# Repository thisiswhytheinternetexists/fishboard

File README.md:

# FishBoard
## An Oak-Based controller for 12 Volts aquarium device control

Basic useful feature list:

- [ ] Switches LED strips on and off on a schedule or triggered by a REST call (REST call works, schedule is untested)
- [X] Allows up to 3 devices to be controlled (channel 1 and 2 work, todo: channel 3 troubleshooting)
- [ ] Manual override using buttons (doesn't currently work, todo: hardware troubleshooting)
- [X] Connects to your existing 2.4GHz WiFi Network for remote control and management (handled by the Oak Config, todo: write guide)
- [ ] Supports an SSD1306 OLED display for status and standalone operation
- [X] Integration with Domoticz (todo: write guide. Is a shell script that does a [particle API call](https://docs.particle.io/reference/firmware/photon/#particle-function-))

BOM:

| Manufacturer       | P/N            | Amount |
| ------------------ | -------------- | ------ |
| Multicomp          | MJ-179PH       | 1      |
| Fairchild          | FQP30N06L      | 3      |
| Multicomp          | 1N5819         | 3      |
| WURTH Elektronik   | 61300911121    | 2      |
| DigiStump          | Oak            | 1      |
| TE Connectivity    | CFR16J10K      | 1      | 
| Molex              | 22-23-2021     | 7      |
| Molex              | 22-01-2027     | 7      |
| Molex              | 08-50-0032     | 14     |
| Multicomp          | R13-24AL-05-BB | 4      |
| DELTRON ENCLOSURES | 479-0140-0     | 1      |
| Pro Power          | PPW00030       | 2      |
 
Total BOM cost (excluding Oak and PCB) is roughly about EUR14.

Datasheet for MOSFET: http://www.mouser.com/ds/2/149/FQP30N06L-244344.pdf
Datasheet for enclosure: http://www.farnell.com/datasheets/1792140.pdf

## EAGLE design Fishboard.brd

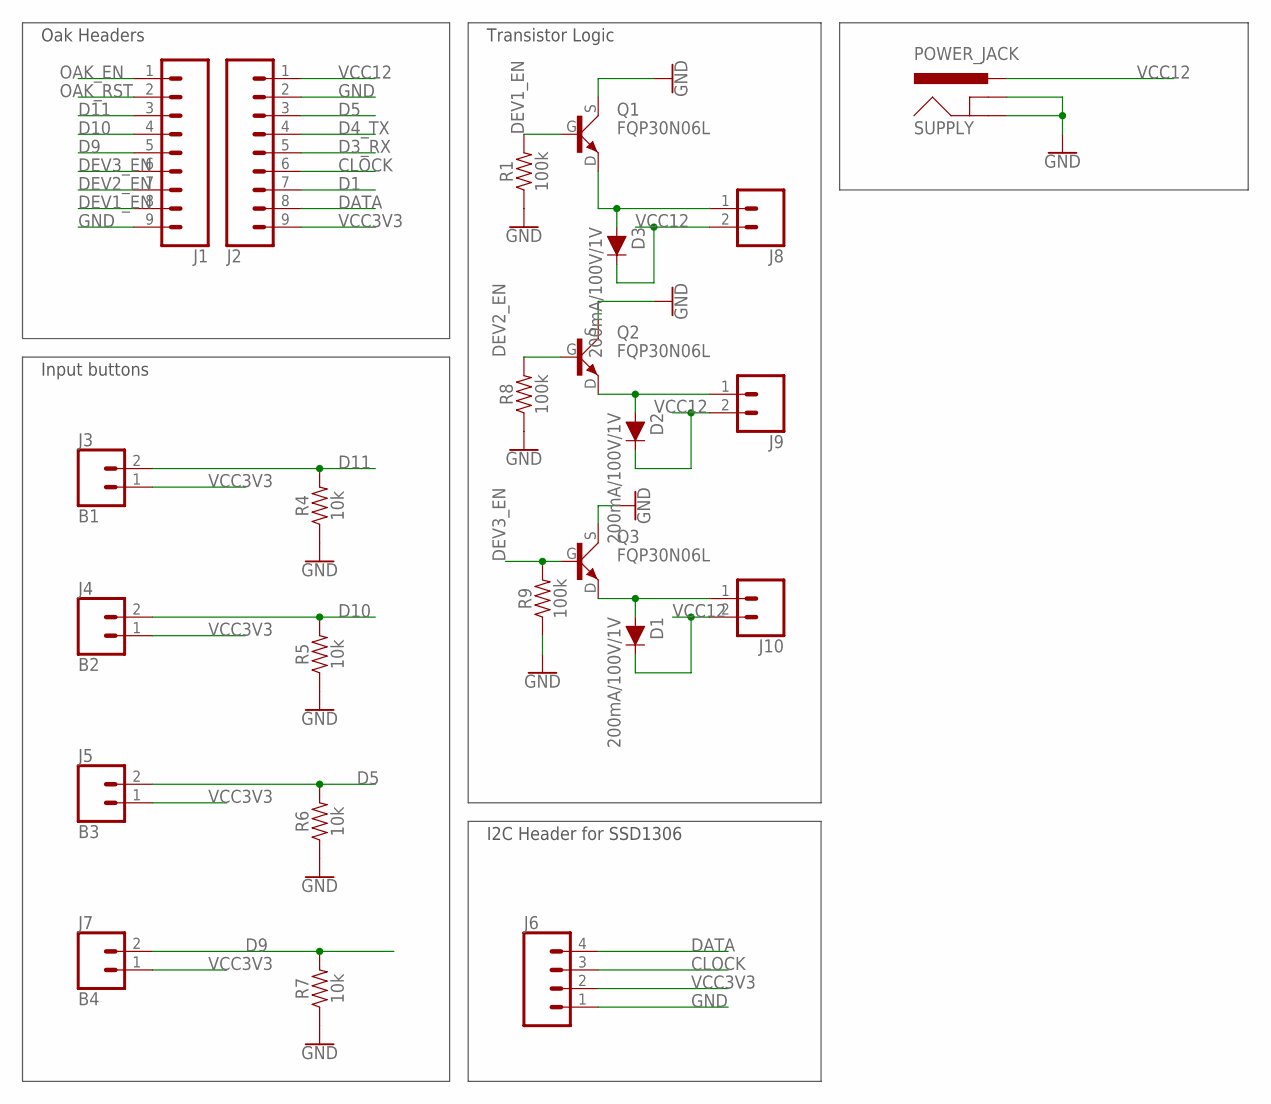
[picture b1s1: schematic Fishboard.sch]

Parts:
D1, D2, D3: 200mA/100V/1V; DIODE-1N4148-KIT
J1, J2: CONN_09LOCK; 1X09_LOCK
J3: B1; 1X02_LOCK
J4: B2; 1X02_LOCK
J5: B3; 1X02_LOCK
J6: CONN_04LOCK; 1X04_LOCK
J7: B4; 1X02_LOCK
J8, J9, J10: CONN_02PTH3; 1X02_LONGPADS
Q1, Q2, Q3: FQP30N06L; TO220
R1, R8, R9: 100k; AXIAL-0.3
R4, R5, R6, R7: 10k; AXIAL-0.3
SUPPLY: POWER_JACK; POWER_JACK_PTH

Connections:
CLOCK: J2.6, J6.3
D1: J2.7
D3_RX: J2.5
D4_TX: J2.4
D5: J2.3, J5.2, R6.P$2 (2)
D9: J1.5, J7.2, R7.P$2 (2)
D10: J1.4, J4.2, R5.P$2 (2)
D11: J1.3, J3.2, R4.P$2 (2)
DATA: J2.8, J6.4
DEV1_EN: J1.8, Q1.G (1), R1.P$2 (2)
DEV2_EN: J1.7, Q2.G (1), R8.P$2 (2)
DEV3_EN: J1.6, Q3.G (1), R9.P$2 (2)
GND: J1.9, J2.2, J6.1, Q1.S (3), Q2.S (3), Q3.S (3), R1.P$1 (1), R4.P$1 (1), R5.P$1 (1), R6.P$1 (1), R7.P$1 (1), R8.P$1 (1), R9.P$1 (1), SUPPLY.GND, SUPPLY.GNDBREAK
unnamed: D2.A, J9.1, Q2.D (2)
unnamed: D3.A, J8.1, Q1.D (2)
unnamed: D1.A, J10.1, Q3.D (2)
OAK_EN: J1.1
OAK_RST: J1.2
VCC3V3: J2.9, J3.1, J4.1, J5.1, J6.2, J7.1
VCC12: D1.C, D2.C, D3.C, J2.1, J8.2, J9.2, J10.2, SUPPLY.PWR

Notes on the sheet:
Oak Headers
Input buttons
I2C Header for SSD1306
Transistor Logic

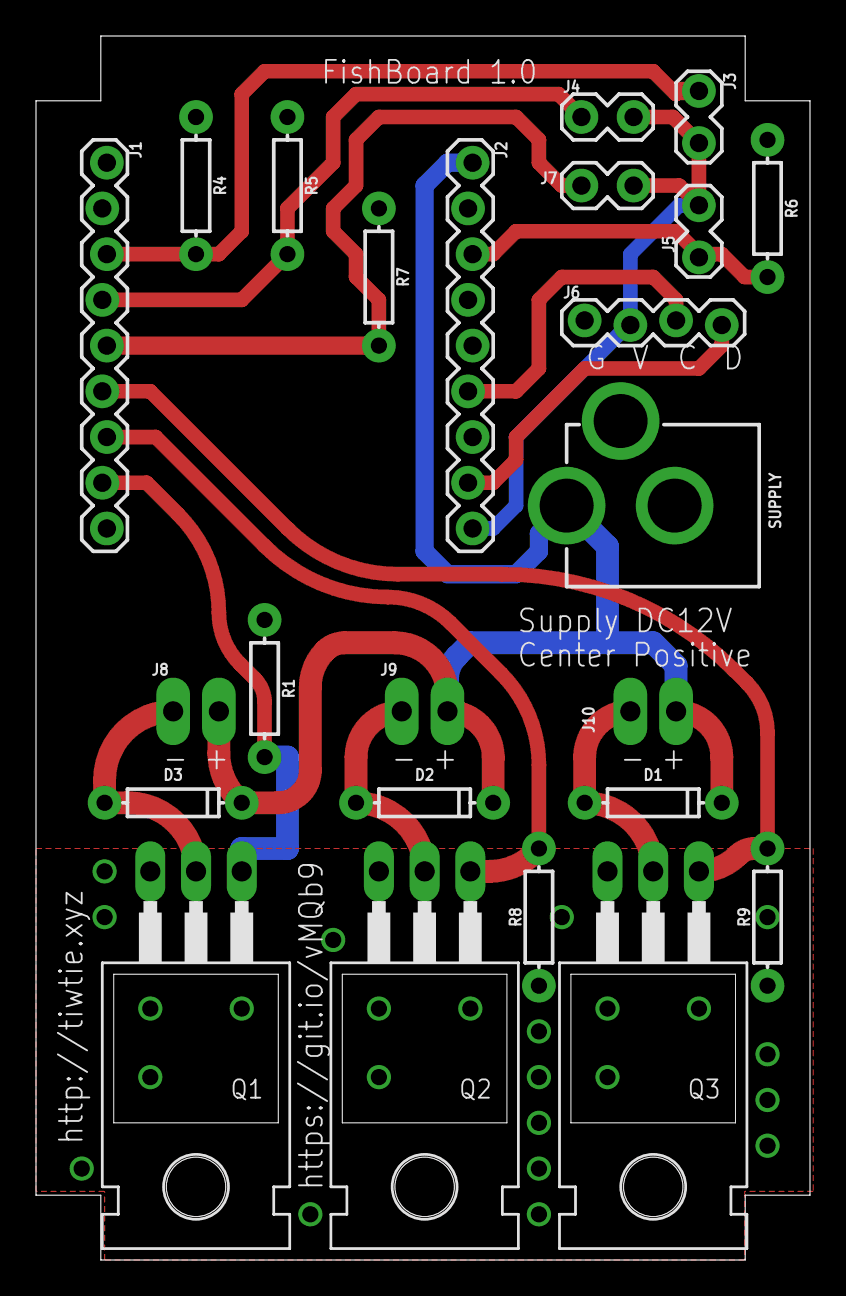
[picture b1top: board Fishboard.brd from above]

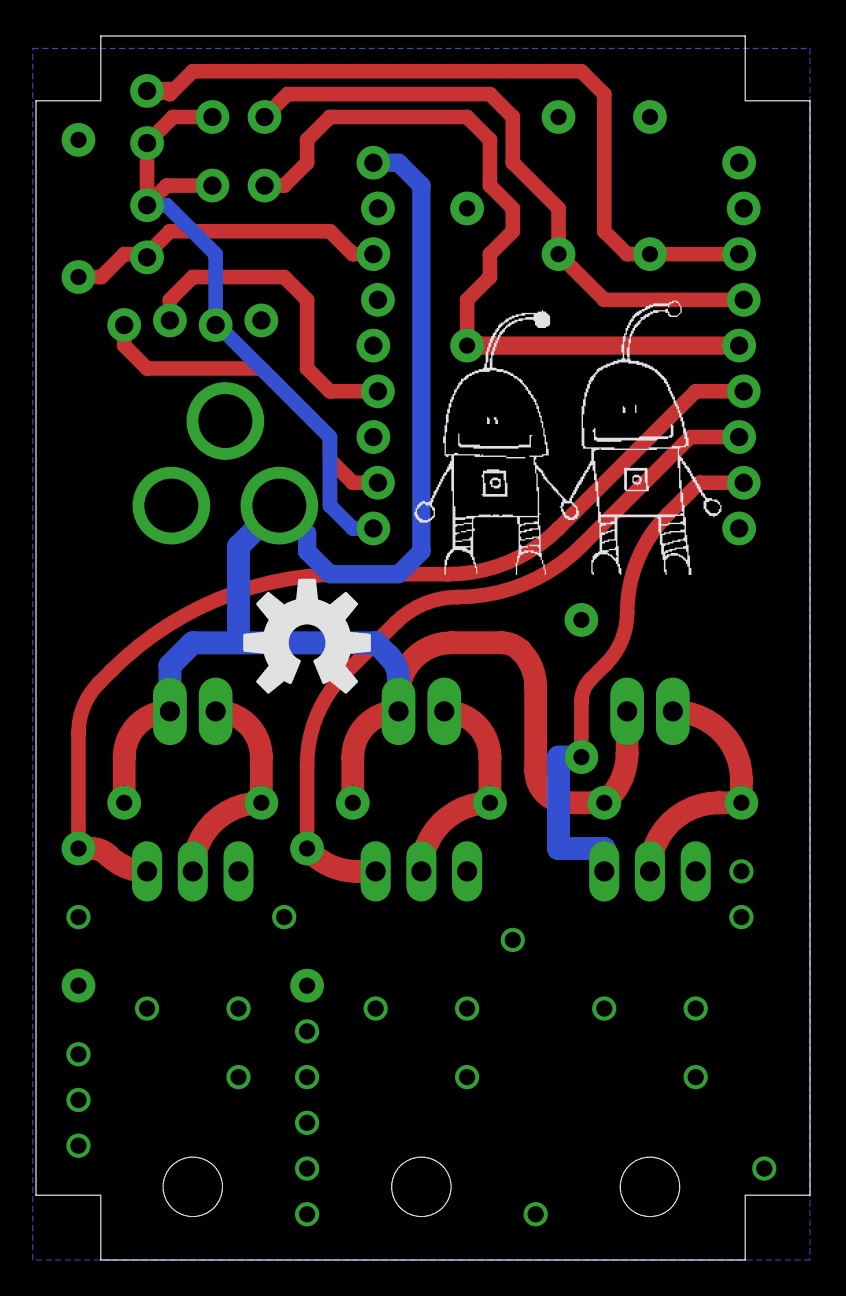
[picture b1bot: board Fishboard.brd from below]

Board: 2 copper layers, 43.0 x 68.0 mm, 26 parts (2 on the bottom side), 15 nets.

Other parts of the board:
U$1: TIWTIE_LOGO
U$2: OSHW-LOGO-L

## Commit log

2017-01-22 Initial commit. I'll have this reviewed by someone before sending it off to the fab :)
2017-01-22 Reorganized schematics
2017-01-22 Switched the TIP120 with a logic level MOSFET (FQP30N06L). The current limiting resistors have been replaced with pulldowns.
2017-01-22 Added library with a custom part
2017-01-22 Replaced TIP120 part with custom part so that we can correctly route it.
2017-01-22 Added reference to MOSFET datasheet in README.md
2017-01-29 Moved Open Source Hardware logo to bottom of board. Added flyback diodes.
2017-01-29 Changed the board size and rerouted everything to make the board fit the case I selected
2017-01-29 Update readme to include BOM
2017-01-29 Change the net for the gndplane-connecting vias to GND. Renamed a FET to Q3 instead of U$3.
2017-02-11 I've tested the board with an arduino sketch. And it works! #awesome. Placed an order for 3x the PCB to see if that will work as well!
2017-02-11 Updated sketch with NTP support a well as alarm functionality that allows us to call a function on a schedule.
2017-02-11 Implemented remote function call for setting channel 1 state.
2017-03-04 Added channel 2 and channel 3 control
2017-03-04 Disable the alarm (for now)
2017-03-04 Reformat readme BOM table
2017-03-04 Updated readme to reflect current state of the project

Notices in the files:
parts and their libraries:
SparkFun-Connectors: Licensing: Creative Commons ShareAlike 4.0 International - https://creativecommons.org/licenses/by-sa/4.0
